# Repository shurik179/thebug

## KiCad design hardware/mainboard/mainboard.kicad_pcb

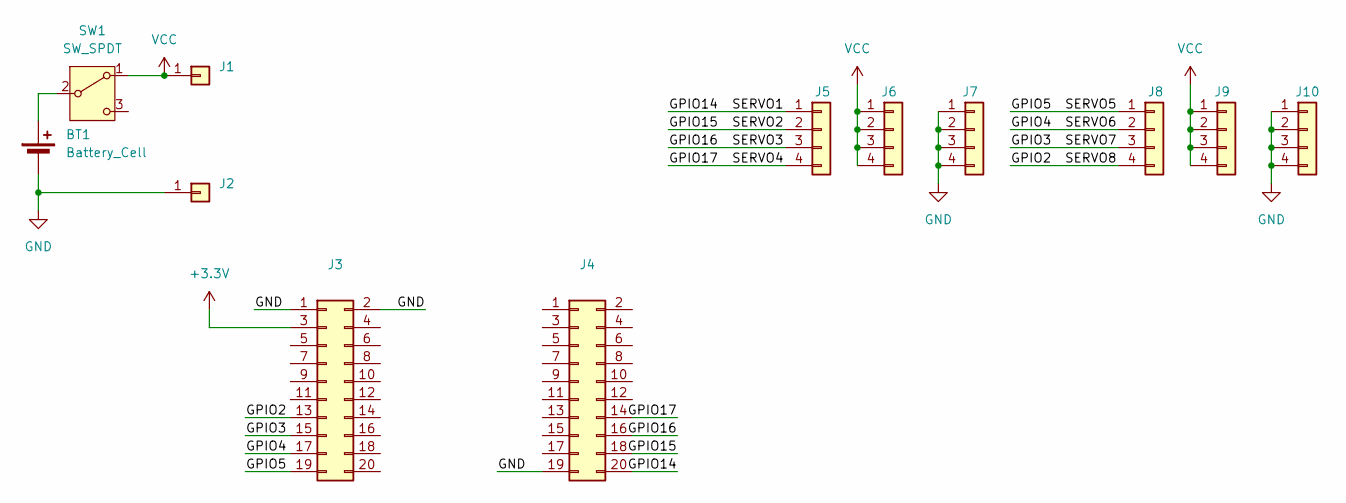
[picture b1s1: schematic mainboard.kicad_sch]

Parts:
BT1: Battery_Cell; BatteryHolder_Bulgin_BX0123_1xCR123
J1, J2: Conn_01x01; SolderWirePad_1x01_SMD_2x4mm
J3, J4: Conn_02x10_Odd_Even; PinHeader_2x10_P1.27mm_Vertical_SMD
J5, J8: Conn_01x04; PinHeader_1x04_P2.54mm_Horizontal
J6, J7, J9, J10: Conn_01x04; PinHeader_1x04_P2.54mm_Vertical
SW1: SW_SPDT; SW_SPDT_GSWITCH_MS-22D28

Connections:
+3.3V: J3.3
/GPIO2: J3.13, J8.4
/GPIO3: J3.15, J8.3
/GPIO4: J3.17, J8.2
/GPIO5: J3.19, J8.1
/GPIO14: J4.20, J5.1
/GPIO15: J4.18, J5.2
/GPIO16: J4.16, J5.3
/GPIO17: J4.14, J5.4
GND: BT1.2 (-), J2.1, J3.1, J3.2, J4.19, J7.1, J7.2, J7.3, J7.4, J10.1, J10.2, J10.3, J10.4
unnamed: BT1.1 (+), SW1.2 (B)
VCC: J1.1, J6.1, J6.2, J6.3, J6.4, J9.1, J9.2, J9.3, J9.4, SW1.1 (A)

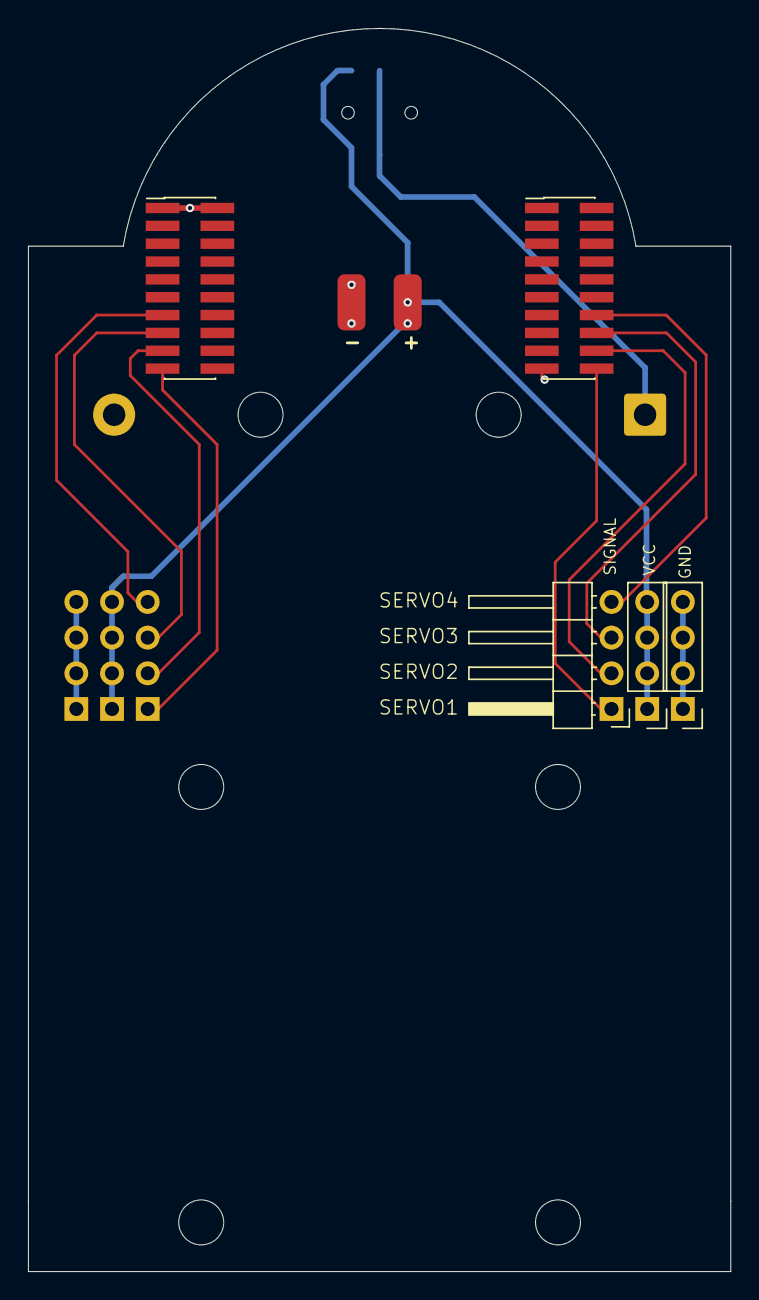
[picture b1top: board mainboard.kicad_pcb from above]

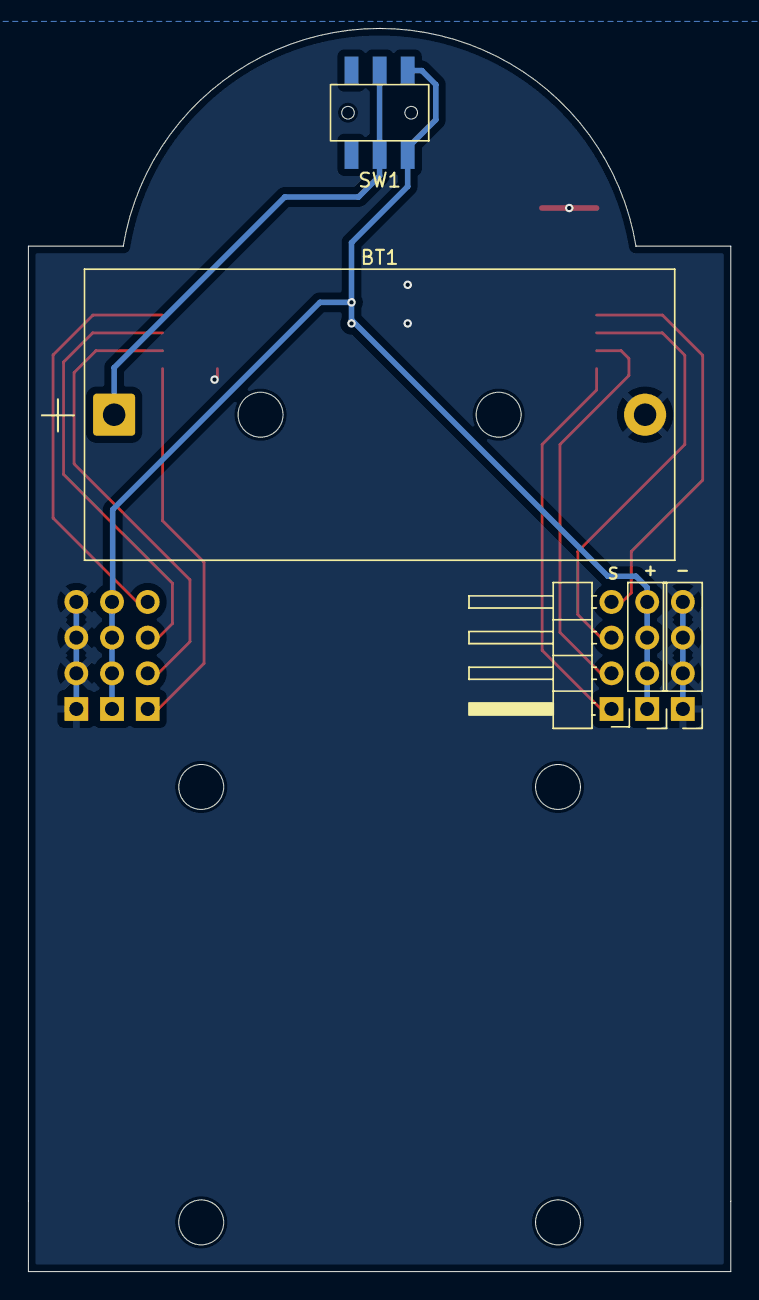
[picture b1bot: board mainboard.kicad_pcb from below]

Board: 2 copper layers, 50.0 x 88.5 mm, 12 parts (5 on the bottom side), 11 nets.
